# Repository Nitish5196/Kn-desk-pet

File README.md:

# Kn desk pet ( DESK-ORPH)
Desk Orph is a portable deskpet with a ESP32-S3 , a round GC9A01 display , TP4056 type C charger , a pazzive buzzer , Metal power switch  , 2 push buttons , a custom PCB and a 1000mAh rechargable battery . customize it  to make your very own desk pet :3

You can basically code it to code anything you want but im just making it do simple taks like showing the To-Do list , showing selective notifications from your phone and act as a alarm clock too. 
## PCB and Schematic

## Animation/Art

## BOM: 

| Part | Qty | Unit | Total | Link |
| --- | --- | --- | --- | --- |
| ESP32-S3 DevKit | 1 | $10.13 | $10.13 | https://www.amazon.in/OceanLabz-ESP32-S3-DevKit-N16R8-MicroPython-Unsoldered/dp/B0F9XB91XG/ref=sr_1_5?crid=1G0OY53KWR6BK&dib=eyJ2IjoiMSJ9.zjUp9SL683q9W3uyF354cuWWZeAE9XPlOSGDfnoeWudk8t3GRA8UuNwYVbu0mKYuyhRK6mLEz3rXj2izIy6QzLVV0bhIhzcQGhPA3Q9-ttGfDcAY80otmx4exqhnPDa8HHlxwS45stbhcj5UdVMDePCQJKNugmUbLa9yzyPOZk_99rDhtOCwfp6EJOdZO-MI5__koZ3nfXhz8uL1eTZt4jcjMVgLrWstaP1U4--AexY2V3qft1FluYwzD-w9p6YX_B52r8EuG64BOw3nBsypi11aW0fe7h8_wH8u3Xna7-w.vhQx7T2ZtLYWMO7Q6XMFm8dWrsnzzQLhLh4NF0P5mYI&dib_tag=se&keywords=esp32+s3+devkit&qid=1791373567&sprefix=ESP32+S3+de%2Caps%2C630&sr=8-5 |
| Round Display | 1 | $5.29 | $5.29 | https://robu.in/product/goldenmorning-gc9a01-7p-240x240-spi-1-28-inch-round-display-module/ |
| TP4056 Type-C Charger | 1 | $0.20 | $0.20 | https://robu.in/product/tp4056-1a-li-ion-lithium-battery-charging-module-with-current-protection-type-c/ |
| Passive Buzzer | 1 | $0.51 | $0.51 | https://robu.in/product/1-month-warranty-1248/ |
| Push buttons | 1 | $0.20 | $0.20 | [https://robu.in/product/mts-102-a2t-miniature-toggle-switch-3-pinon-on/](https://robu.in/product/tp4056-1a-li-ion-lithium-battery-charging-module-with-current-protection-type-c/) |
| Power switch | 1 | $0.27 | $0.27 | https://robu.in/product/mts-102-a2t-miniature-toggle-switch-3-pinon-on/ |
| Straight Female Pin Headers | 1 | $1.02 | $1.02 | https://robu.in/product/1-40-pin-2-54m-straight-long-female-berg-strip-connector-pack-of-5/ |
| Battery connector | 1 | $0.62 | $0.62 | https://robu.in/product/jst-male-2-pin-connector-set-10pcsset/ |
| Battery | 1 | $3.80 | $3.80 | https://www.amazon.in/KP-Rechargeable-Battery-902535-Connector/dp/B0DY89KG26/ref=cm_cr_arp_d_product_top?ie=UTF8 |
| PCB | 1 | $10.00 | $10.00 | https://robu.in/product/online-pcb-manufacturing-service/ |
| Total | | | $32.04 |

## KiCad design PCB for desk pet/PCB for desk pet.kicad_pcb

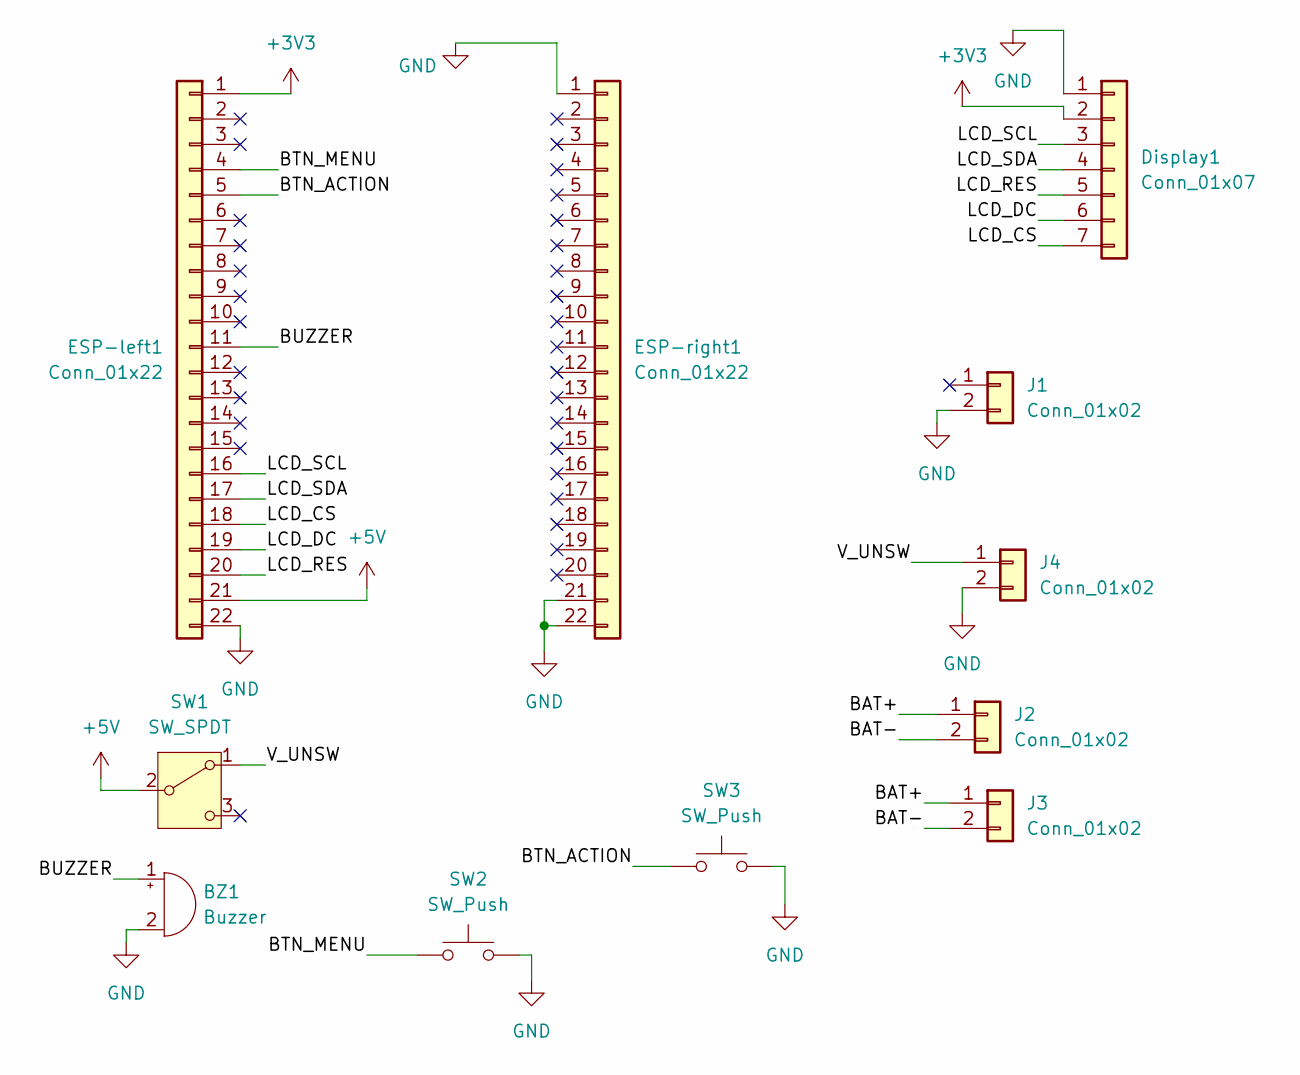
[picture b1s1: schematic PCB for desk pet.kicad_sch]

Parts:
BZ1: Buzzer; Buzzer_12x9.5RM7.6
Display1: Conn_01x07; PinSocket_1x07_P2.54mm_Vertical
ESP-left1: Conn_01x22; PinSocket_1x22_P2.54mm_Vertical
ESP-right1: Conn_01x22; PinSocket_1x22_P2.54mm_Vertical
J1, J2, J4: Conn_01x02; PinHeader_1x02_P2.54mm_Vertical
J3: Conn_01x02; JST_PH_B2B-PH-K_1x02_P2.00mm_Vertical
SW1: SW_SPDT; SW_Toggle_Blue_wSlots
SW2, SW3: SW_Push; SW_PUSH_6mm_H5mm

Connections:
+3V3: Display1.2, ESP-left1.1
+5V: ESP-left1.21, SW1.2 (B)
/BAT+: J2.1, J3.1
/BAT-: J2.2, J3.2
/BTN_ACTION: ESP-left1.5, SW3.1
/BTN_MENU: ESP-left1.4, SW2.1
/BUZZER: BZ1.1 (+), ESP-left1.11
/LCD_CS: Display1.7, ESP-left1.18
/LCD_DC: Display1.6, ESP-left1.19
/LCD_RES: Display1.5, ESP-left1.20
/LCD_SCL: Display1.3, ESP-left1.16
/LCD_SDA: Display1.4, ESP-left1.17
/V_UNSW: J4.1, SW1.1 (A)
GND: BZ1.2 (-), Display1.1, ESP-left1.22, ESP-right1.1, ESP-right1.21, ESP-right1.22, J1.2 (Pin_2_2), J4.2, SW2.2, SW3.2

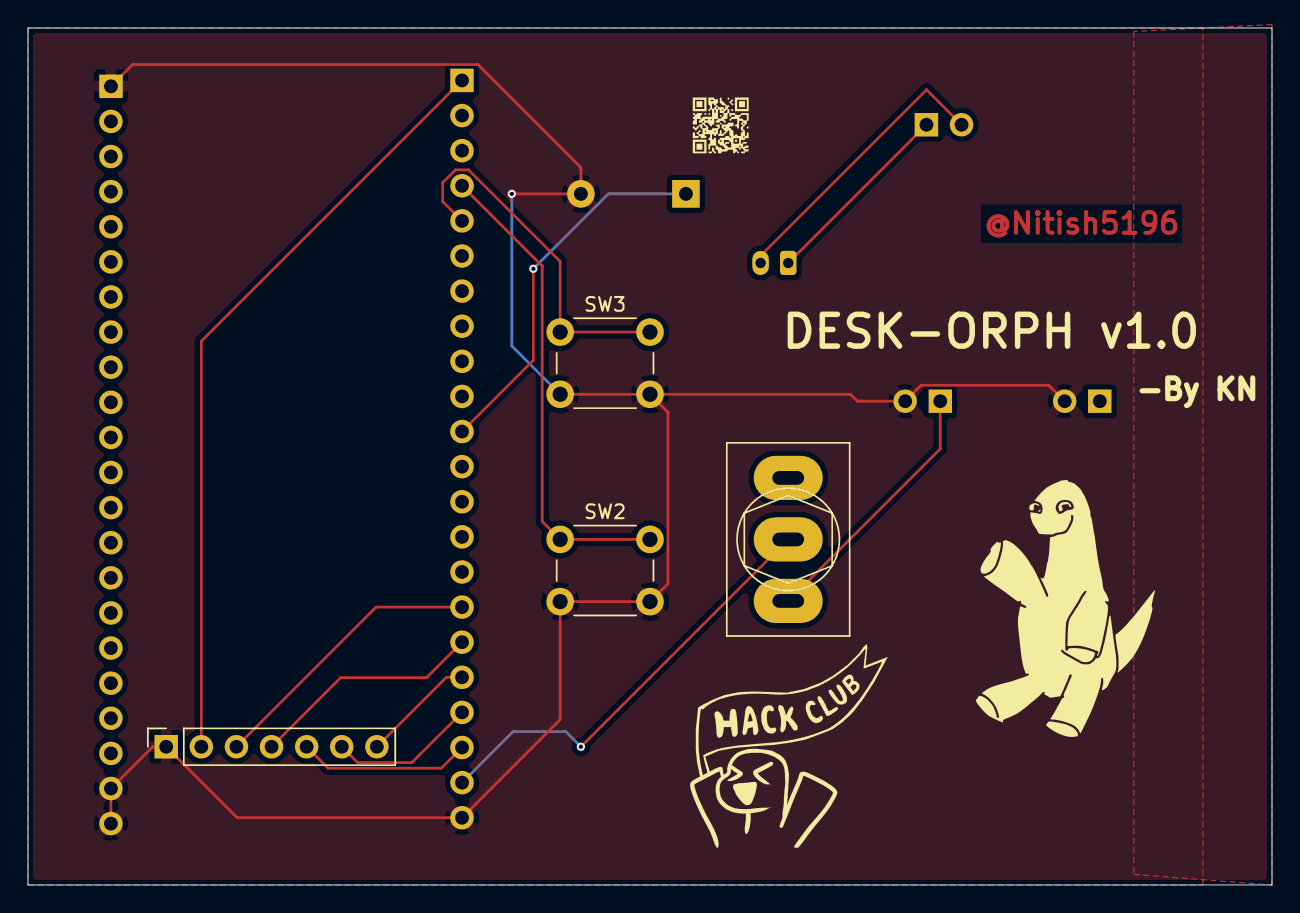
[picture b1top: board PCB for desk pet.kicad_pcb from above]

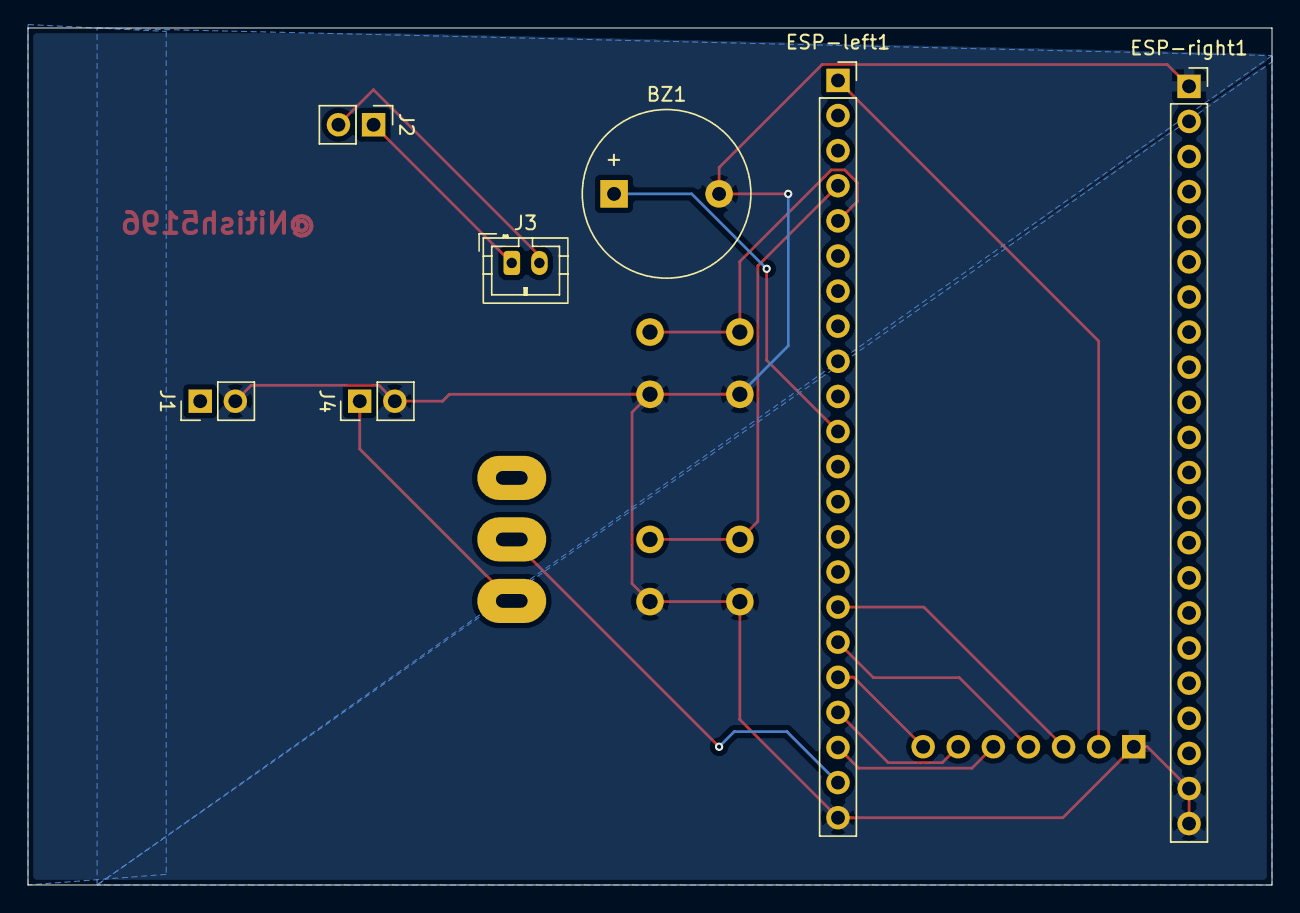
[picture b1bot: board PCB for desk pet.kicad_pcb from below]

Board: 2 copper layers, 90.0 x 62.0 mm, 11 parts (7 on the bottom side), 14 nets.

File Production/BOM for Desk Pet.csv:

"Id";"Designator";"Footprint";"Quantity";"Designation";"Supplier and ref";
1;"BZ1";"Buzzer_12x9.5RM7.6";1;"Buzzer";;;
2;"Display1";"PinSocket_1x07_P2.54mm_Vertical";1;"Conn_01x07";;;
3;"ESP-left1, ESP-right1";"PinSocket_1x22_P2.54mm_Vertical";2;"Conn_01x22";;;
4;"J1, J2, J4";"PinHeader_1x02_P2.54mm_Vertical";3;"Conn_01x02";;;
5;"J3";"JST_PH_B2B-PH-K_1x02_P2.00mm_Vertical";1;"Conn_01x02";;;
6;"SW1";"SW_Toggle_Blue_wSlots";1;"SW_SPDT";;;
7;"SW2, SW3";"SW_PUSH_6mm_H5mm";2;"SW_Push";;;
